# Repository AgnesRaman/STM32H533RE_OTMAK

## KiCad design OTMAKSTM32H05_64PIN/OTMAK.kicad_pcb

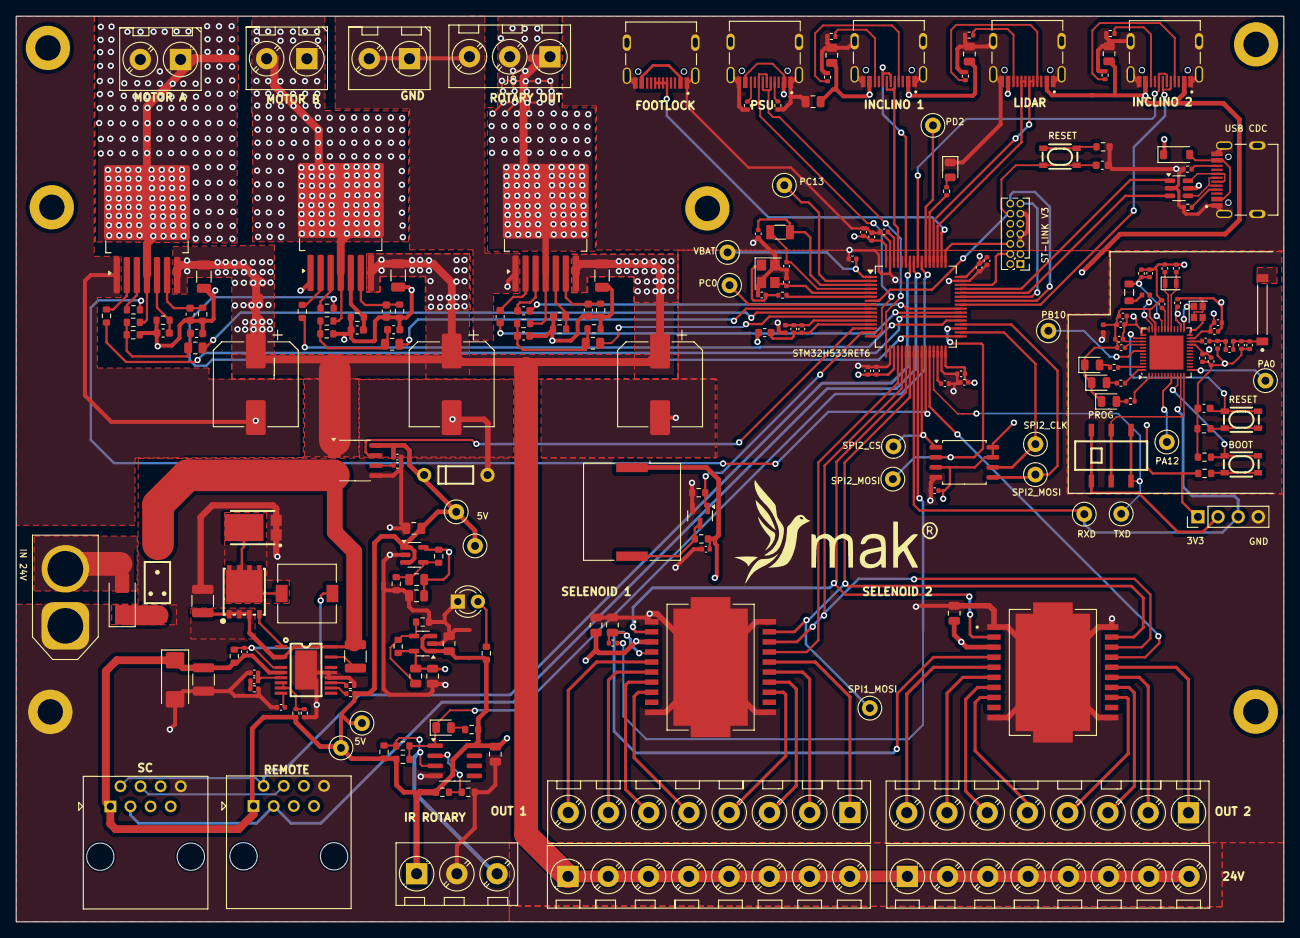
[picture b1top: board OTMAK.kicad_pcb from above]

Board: 4 copper layers, 160.0 x 114.3 mm, 227 parts (0 on the bottom side), 162 nets.

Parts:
ANT1: 2500AT44M0400E; 2500AT44M0400
BZ1: Buzzer; Buzzer_Murata_PKLCS1212E
C1, C33, C48, C53, C67: 100nF; C_0603_1608Metric
C2, C3: 24pF; C_0402_1005Metric
C4, C5: 5pF; C_0402_1005Metric
C6, C7: 2.2uF; C_0402_1005Metric
C8, C9, C10, C11, C16, C19, C29, C30, C31, C32, C34, C41, C45, C58: 100nF; C_0402_1005Metric
C12, C13, C14, C15, C69, C70: 1uF; C_0402_1005Metric
C17: 1UF; C_0402_1005Metric
C18: 10uF; C_0402_1005Metric
C20: 0.1uF; C_0805_2012Metric
C22, C23, C54, C75: 4.7uF; C_0805_2012Metric
C24, C25, C26, C60: 22uF; C_0805_2012Metric
C27, C50, C68: 1nF; C_0603_1608Metric
C28, C38: 4.7uF; C_0402_1005Metric
C35: 220nF; C_0402_1005Metric
C36, C37: 8pF; C_0402_1005Metric
C39: 3.4pF; C_0402_1005Metric
C40: 1.2pF; C_0402_1005Metric
C42, C44: 0.5pF; C_0402_1005Metric
C43, C46, C47: 3pF; C_0402_1005Metric
C49, C56, C65: 1uF; C_0603_1608Metric
C51, C59, C64: 100nF; C_1206_3216Metric
C52, C62, C63: 470uF/1000uF; CP_Elec_10x10.5
C55, C57, C76, C88: 4.7nF; C_0805_2012Metric
C66: 1uF; C_0805_2012Metric
C71: 3.3nF; C_0402_1005Metric
C72: 0.47uF; C_1210_3225Metric
C73: 47pF; C_0402_1005Metric
C74: 12uF; C_1210_3225Metric
C77: 0.1uF; C_0402_1005Metric
C78: 1nF; C_0402_1005Metric
C80: 330uF; CP_EIA-6032-15_Kemet-U
C83: 10uF; C_1210_3225Metric
COM-TO-STM1: SW-SMD_SS-3235S-L2
D1, D3, D4, D5: LED; LED_0805_2012Metric
D2: D; D_SOD-123
D6: D; LED_0805_2012Metric
D7: 1N5819; D_SMA
D8: S310; POWERDI-5_L5.4-W4.0-LS6.5-RD
D10: LED; LED_D3.0mm
F1: Fuse; RES-SMD_SA72SB0
FB1: 600 @ 100mhz; L_0603_1608Metric
H1, H3, H4, H5, H6, H7: MountingHole; MountingHole_3.2mm_M3_DIN965_Pad
J1, J2, J3, J4, J5, J14: TYPE-C-31-M-12; HRO_TYPE-C-31-M-12
J7: STLink; PinHeader_2x07_P1.27mm_Vertical
J8: ROTARY; TerminalBlock_3_Pin
J9: RX_DEBUG; TestPoint_Loop_D2.50mm_Drill1.0mm
J10: TX_DEBUG; TestPoint_Loop_D2.50mm_Drill1.0mm
J11: Conn_01x01; TestPoint_Loop_D2.50mm_Drill1.0mm
J12, J13, J15, J16: Conn_01x08; TerminalBlock_8_pin
J17: PROG; PinHeader_1x04_P2.54mm_Vertical
J18: IR Interrupt; TerminalBlock_3_Pin
J19, J20, J22: Conn_01x02; TerminalBlock_2_Pin
J21: 24V INPUT; AMASS_XT60-F_1x02_P7.20mm_Vertical
L1, L2: L; L_0402_1005Metric
L3: 10uH; L_0805_2012Metric
L4: 22nH; L_0402_1005Metric
L5: 3n; L_0402_1005Metric
L6: 22uH; L_7.3x7.3_H3.5
Q1: BSS138; SOT-23
R1, R2, R5, R7, R8, R9, R10, R12, R35, R38: 5k1; R_0402_1005Metric
R3, R18, R20: 100R; R_0603_1608Metric
R4: 47R; R_0402_1005Metric
R6, R33: 52.3K; R_0603_1608Metric
R11: 3M3; R_0603_1608Metric
R13, R17, R28, R58, R59, R63: 1K; R_0603_1608Metric
R14, R34: 30.1K; R_0603_1608Metric
R15: 100R; R_0402_1005Metric
R16, R23, R24, R25: 1K; R_0402_1005Metric
R19, R26: 10K; C_0603_1608Metric
R21: 100K; R_0603_1608Metric
R27, R37, R53: 0.51K; R_0603_1608Metric
R29, R40, R49: 3.9K; R_0603_1608Metric
R30, R45, R47: 33K; R_0603_1608Metric
R31, R36, R50, R51, R52, R54, R55, R56, R57: 10K; R_0603_1608Metric
R32, R46, R48: 0R; R_0805_2012Metric
R60: 5.76K; R_0402_1005Metric
R61: 36.5K; R_0402_1005Metric
R62: 20mR; R_0603_1608Metric
R64: 100K; R_0402_1005Metric
R65: 422K; R_0402_1005Metric
R66: 80.6K; R_0402_1005Metric
Remote1: RJ45; RJ45_OST_PJ012-8P8CX_Vertical
SC1: RJ45; RJ45_OST_PJ012-8P8CX_Vertical
SW1, SW3: EN; KEY-SMD_4P-L4.2-W3.2-P2.20-LS4.6
SW4: BOOT_; KEY-SMD_4P-L4.2-W3.2-P2.20-LS4.6
TP1, TP2, TP3, TP4, TP5, TP6, TP7, TP8, TP9, TP10, TP11, TP12, TP13, TP14, TP15: TestPoint_Loop_D2.50mm_Drill1.0mm
U1: LQFP-64_10x10mm_P0.5mm
U2: W25Q128JVSIQ; SOIC-8_5.275x5.275mm_P1.27mm
U3, U5: IC_L6201PS
U4, U8: TPS73601DBVR; TSOT-23-5
U6: QFN48; QFN-48-1EP_6x6mm_P0.4mm_EP4.3x4.3mm
U7, U9, U10: TO-263-7_TabPin8
U11: LM393; SOIC-8_3.9x4.9mm_P1.27mm
U12: CC6900SO-20A; SOP-8_3.9x4.9mm_P1.27mm
U13: TSSOP-20_L6.5-W4.4-P0.65-BL-EP
U14: AP3P3R0MT
U16: USBLC6-2SC6; SOT-23-6
Y1: 24MHz, 6pF; Crystal_SMD_3225-4Pin_3.2x2.5mm
Y2: 32.768 kHz; Crystal_SMD_3215-2Pin_3.2x1.5mm
Y3: 32.7680 KHz 12.5 pF; Crystal_SMD_2012-2Pin_2.0x1.2mm
Y4: 32.0000 MHz 8pF; Crystal_SMD_2016-4Pin_2.0x1.6mm
ZD1: BZX55C5V1; DO-35_BD2.0-L4.0-P8.00-D0.5-FD

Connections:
3.3VA: C55.1, C57.1, FB1.1, R33.1, U8.5 (OUT)
3V3: BZ1.1 (-), C8.2, C9.2, C10.2, C11.2, C12.2, C13.2, C14.2, C15.2, C18.2, C19.1, C30.1, C32.2, C34.2, C38.2, C41.2, C43.2, C45.1, C47.1, C76.1, C88.1, J7.3, J17.1, R6.1, R13.2, R18.1, U1.19 (VDD), U1.32 (VDD), U1.48 (VDD), U1.64 (VDD), U2.3 (~WP), U2.7 (~HOLD), U2.8 (VCC), U4.5 (OUT), U6.21 (VDD2), U6.23 (VDDRF), U6.26 (VDD4), U6.36 (VDDSD), U6.37 (VDD3), U6.39 (VDD1)
5V: C22.1, C23.1, C24.1, C25.1, C26.1, C54.1, C60.1, C66.1, C69.1, C75.1, C78.2, C80.1, C83.1, D2.1 (K), J1.A4B9 (VBUS), J1.B4A9 (VBUS), J2.A4B9 (VBUS), J2.B4A9 (VBUS), J3.A4B9 (VBUS), J3.B4A9 (VBUS), J14.A4B9 (VBUS), J14.B4A9 (VBUS), J18.1, R50.1, R51.1, R57.1, R59.1, R62.2, R63.1, R64.2, R65.2, Remote1.1, SC1.1, TP7.1, TP9.1, TP11.1, TP12.1, U3.3 (VDD), U4.1 (IN), U4.3 (EN), U5.3 (VDD), U8.1 (IN), U8.3 (EN), U11.8 (V+), U12.8 (VCC), U13.6 (SENSE-), U16.5 (VBUS), ZD1.2 (K)
/OSCIN: C2.2, U1.5 (PH0-OSC_IN), Y1.3
/OSCOUT: R4.2, U1.6 (PH1-OSC_OUT)
ADC1_INP0: U1.14 (PA0), U12.7 (VIOUT)
ADC1_INP12: R48.1, U1.10 (PC2)
ADC2_INP11: R46.1, U1.9 (PC1)
ADC2_INP13: R32.1, U1.11 (PC3)
BOOTA: R21.1, SW4.1, SW4.2, U6.10 (PA10)
C_D+: J5.A6 (DP1), J5.B6 (DP2), U16.6 (I/O1)
C_D-: J5.A7 (DN1), J5.B7 (DN2), U16.4 (I/O1)
GNDREF: C28.2, C29.2, C30.2, C31.2, C32.1, C33.2, C34.1, C35.1, C36.2, C37.2, C38.1, C40.1, C41.1, C43.1, C44.1, C45.2, C46.1, C47.2, D3.1 (K), D4.1 (K), D5.1 (K), L2.2, R20.2, R21.2, U6.34 (VSS), U6.49 (GND), Y4.2, Y4.4
I2C1_SCL: J1.A7 (DN1), J1.B7 (DN2), U1.61 (PB8)
I2C1_SDA: J1.A6 (DP1), J1.B6 (DP2), U1.59 (PB7)
I2C3_SCL: J3.A7 (DN1), J3.B7 (DN2), U1.41 (PA8)
I2C3_SDA: J3.A6 (DP1), J3.B6 (DP2), U1.56 (PB4)
IN-24V: C51.1, C52.1, C59.1, C62.1, C63.1, C64.1, J13.1, J13.2, J13.3, J13.4, J13.5, J13.6, J13.7, J13.8, J16.1, J16.2, J16.3, J16.4, J16.5, J16.6, J16.7, J16.8, U7.7 (VS), U9.7 (VS), U10.7 (VS), U12.1 (IP+), U12.2 (IP+)
INPUT_Foot_LOCK: J4.A6 (DP1), J4.A7 (DN1), J4.B6 (DP2), J4.B7 (DN2), U1.50 (PA15)
INT: Remote1.4, SC1.4
LD1: R16.1, U1.53 (PC12)
MOTOR_A: J19.1, J19.2, R45.1, U9.4 (OUT), U9.8 (OUT)
MOTOR_B: J20.1, J20.2, R47.1, U10.4 (OUT), U10.8 (OUT)
NRST: C1.2, J7.12, SW1.1, SW1.2, U1.7 (NRST)
unnamed: ANT1.1 (Feeding_Point), C42.2, C44.2, C46.2, L5.2
unnamed: BZ1.2 (+), Q1.3 (D), R13.1
unnamed: C3.2, R4.1, Y1.1
unnamed: C39.2, C40.2, C42.1, L5.1
unnamed: C49.1, R29.1, R30.2, R32.2
unnamed: C56.1, R40.1, R45.2, R46.2
unnamed: C65.1, R47.2, R48.2, R49.1
unnamed: C71.2, R60.2
unnamed: D1.2 (A), R16.2
unnamed: D2.2 (A), J5.A4B9 (VBUS), J5.B4A9 (VBUS)
unnamed: D3.2 (A), R23.2
unnamed: D4.2 (A), R24.2
unnamed: D5.2 (A), R25.2
unnamed: D6.2 (A), R59.2
unnamed: D7.2 (A), J21.2
unnamed: D7.1 (K), F1.1
unnamed: D8.3 (K), L6.1, U14.5 (D), U14.6 (D), U14.7 (D), U14.8 (D), U14.9 (D)
unnamed: D10.2 (A), R63.2
unnamed: J1.A5 (CC1), R1.2
unnamed: J1.B5 (CC2), R5.1
unnamed: J2.A5 (CC1), R2.2
unnamed: J2.B5 (CC2), R7.1
unnamed: J3.A5 (CC1), R9.2
unnamed: J3.B5 (CC2), R10.1
unnamed: J4.A4B9 (VBUS), J4.B4A9 (VBUS)
unnamed: J5.A5 (CC1), R8.2
unnamed: J5.B5 (CC2), R12.1
unnamed: J14.A5 (CC1), R35.2
unnamed: J14.B5 (CC2), R38.1
unnamed: COM-TO-STM1.1, COM-TO-STM1.4, J17.2
unnamed: J18.3, R50.2, R54.1, U11.3 (+)
unnamed: L3.2, L4.2
unnamed: R3.1, SW1.3, SW1.4
unnamed: R18.2, SW4.3, SW4.4
unnamed: R20.1, SW3.3, SW3.4
unnamed: C4.2, U1.3 (PC14-OSC32_IN), Y2.2
unnamed: C5.2, U1.4 (PC15-OSC32_OUT), Y2.1
unnamed: C58.1, TP1.1, U1.1 (VBAT)
unnamed: C76.2, R6.2, R14.1, U4.4 (NR/FB)
unnamed: U6.25 (OSCIN), Y4.1
unnamed: U6.24 (OSCOUT), Y4.3
unnamed: TP13.1, U6.13 (PA0)
unnamed: TP15.1, U6.8 (PA12)
unnamed: TP14.1, U6.42 (PB10)
unnamed: C39.1, U6.22 (RF1)
unnamed: C35.2, U6.31 (VCAP)
unnamed: C31.1, U6.40 (VDDA)
unnamed: C28.1, C29.1, L3.1, U6.32 (VFBSD)
unnamed: L4.1, U6.35 (VLXSD)
unnamed: C36.1, U6.30 (XTAL0), Y3.1
unnamed: C37.1, U6.29 (XTAL1), Y3.2
unnamed: R19.2, U7.2 (IN)
unnamed: R26.2, U7.3 (INH)
unnamed: C27.1, R17.2, U7.6 (IS)
unnamed: C48.1, R27.2, U7.5 (SR)
unnamed: C55.2, R33.2, R34.1, U8.4 (NR/FB)
unnamed: R31.2, U9.2 (IN)
unnamed: R36.2, U9.3 (INH)
unnamed: C50.1, R28.2, U9.6 (IS)
unnamed: C53.1, R37.2, U9.5 (SR)
unnamed: R56.1, U10.2 (IN)
unnamed: R55.1, U10.3 (INH)
unnamed: C68.1, R58.2, U10.6 (IS)
unnamed: C67.1, R53.2, U10.5 (SR)
unnamed: R51.2, R52.1, U11.2 (-)
unnamed: C70.1, U12.6 (FILTER)
unnamed: C72.2, U13.18 (CAP)
unnamed: R61.2, U13.13 (FREQ)
unnamed: U13.1 (GATE), U14.4 (G)
unnamed: C71.1, C73.1, U13.7 (ITH)
unnamed: R64.1, U13.12 (PGOOD)
unnamed: R65.1, R66.2, U13.8 (PGUV), U13.9 (VFB)
unnamed: C72.1, C74.1, F1.2, U12.3 (IP-), U12.4 (IP-), U13.3 (RUN), U13.20 (VIN), U14.1 (S), U14.2 (S), U14.3 (S)
unnamed: C78.1, L6.2, R62.1, U13.5 (SENS+)
unnamed: C77.1, U13.10 (TRACK/SS)
OUT0: J12.1, U3.16 (OUT0)
OUT0A: J15.1, U5.16 (OUT0)
OUT1: J12.2, U3.15 (OUT1)
OUT1A: J15.2, U5.15 (OUT1)
OUT2: J12.3, U3.14 (OUT2)
OUT2A: J15.3, U5.14 (OUT2)
OUT3: J12.4, U3.13 (OUT3)
OUT3A: J15.4, U5.13 (OUT3)
OUT4: J12.5, U3.8 (OUT4)
OUT4A: J15.5, U5.8 (OUT4)
OUT5: J12.6, U3.7 (OUT5)
OUT5A: J15.6, U5.7 (OUT5)
OUT6: J12.7, U3.6 (OUT6)
OUT6A: J15.7, U5.6 (OUT6)
OUT7: J12.8, U3.5 (OUT7)
OUT7A: J15.8, U5.5 (OUT7)
PB3_LED: R25.1, U6.1 (PB3)
PB4_LED: R24.1, U6.48 (PB4)
PB5_LED: R23.1, U6.47 (PB5)
PC0: TP8.1, U1.8 (PC0)
PC13: TP10.1, U1.2 (PC13)
PD2: TP2.1, U1.54 (PD2)
RESET: C20.1, R15.2, U3.4 (RESET), U5.4 (RESET)
ROTARY_DC_OUT: J8.1, J8.2, R30.1, U7.4 (OUT), U7.8 (OUT)
RSTN: C33.1, SW3.1, SW3.2, U6.38 (RSTN)
Rotary_GPIO_Read: D6.1 (K), R54.2, R57.2, U1.55 (PB3), U11.1
SPI1_CS1: U1.20 (PA4), U3.17 (CE)
SPI1_CS2: U1.28 (PB2), U5.17 (CE)
SPI1_MISO: U1.22 (PA6), U3.2 (SO), U5.2 (SO)
SPI1_MOSI: J11.1, U1.23 (PA7), U3.19 (SI), U5.19 (SI)
SPI1_RESET: R15.1, U1.25 (PC5)
SPI1_SCK: U1.21 (PA5), U3.18 (SCLK), U5.18 (SCLK)
SPI2_CLK: TP4.1, U1.34 (PB13), U2.6 (SCK)
SPI2_CS: TP3.1, U1.26 (PB0), U2.1 (~CS)
SPI2_MISO: TP6.1, U1.35 (PB14), U2.2 (DO(IO1))
SPI2_MOSI: TP5.1, U1.36 (PB15), U2.5 (DI(IO0))
SWCLK: J7.6, U1.49 (PA14)
SWDIO: J7.4, U1.46 (PA13)
TIM2_CH2_BUZZER: Q1.1 (G), R11.2, U1.15 (PA1)
TIM3_CH1: R31.1, U1.37 (PC6)
TIM3_CH2: R56.2, U1.38 (PC7)
TIM3_CH3: R19.1, U1.39 (PC8)
TIM3_CH4: R55.2, U1.27 (PB1)
TIM8_CH3: R36.1, U1.33 (PB12)
TIM8_CH4: R26.1, U1.40 (PC9)
UART4_RX_LIDAR: J2.A6 (DP1), J2.B7 (DN2), U1.52 (PC11)
UART4_TX_LIDAR: J2.A7 (DN1), J2.B6 (DP2), U1.51 (PC10)
UART5_RX_SC: Remote1.3, SC1.3, U1.57 (PB5)
UART5_TX_SC: Remote1.2, SC1.2, U1.58 (PB6)
UART_RX: COM-TO-STM1.2, COM-TO-STM1.5, U6.12 (PA8)
USART1_RX_ST-LINK: J7.13, U1.43 (PA10)
USART1_TX_ST-LINK: J7.14, U1.42 (PA9)
USART2_RX_PSU: J14.A7 (DN1), J14.B7 (DN2), U1.17 (PA3)
USART2_TX_PSU: J14.A6 (DP1), J14.B6 (DP2), U1.16 (PA2)
USART3_RX_STM: J9.1, J17.3, U1.24 (PC4), U6.11 (PA9)
USART3_TX_STM: COM-TO-STM1.3, COM-TO-STM1.6, J10.1, U1.29 (PB10)
USB-DM: U1.44 (PA11), U16.3 (I/O2)
USB-DP: U1.45 (PA12), U16.1 (I/O2)
VCAP1: C6.2, U1.30 (VCAP1)
VCAP2: C7.2, U1.62 (VCAP2)
VDDA: C16.2, C17.2, FB1.2, U1.13 (VDDA/VREF+)
VSS: C1.1, C2.1, C3.1, C4.1, C5.1, C6.1, C7.1, C8.1, C9.1, C10.1, C11.1, C12.1, C13.1, C14.1, C15.1, C18.1, C19.2, C20.2, C22.2, C23.2, C24.2, C25.2, C26.2, C27.2, C48.2, C49.2, C50.2, C51.2, C52.2, C53.2, C54.2, C56.2, C57.2, C58.2, C59.2, C60.2, C62.2, C63.2, C64.2, C65.2, C66.2, C67.2, C68.2, C69.2, C70.2, C73.2, C74.2, C75.2, C77.2, C80.2, C83.2, C88.2, D1.1 (K), D8.1 (A), D8.2 (A), D10.1 (K), H3.1, J1.A1B12 (GND), J1.B1A12 (GND), J1.S1 (SHIELD), J1.S2 (SHIELD), J1.S3 (SHIELD), J1.S4 (SHIELD), J2.A1B12 (GND), J2.B1A12 (GND), J2.S1 (SHIELD), J2.S2 (SHIELD), J2.S3 (SHIELD), J2.S4 (SHIELD), J3.A1B12 (GND), J3.B1A12 (GND), J3.S1 (SHIELD), J3.S2 (SHIELD), J3.S3 (SHIELD), J3.S4 (SHIELD), J4.A1B12 (GND), J4.B1A12 (GND), J4.S1 (SHIELD), J4.S2 (SHIELD), J4.S3 (SHIELD), J4.S4 (SHIELD), J5.A1B12 (GND), J5.B1A12 (GND), J5.S1 (SHIELD), J5.S2 (SHIELD), J5.S3 (SHIELD), J5.S4 (SHIELD), J7.5, J7.7, J7.11, J8.3, J14.A1B12 (GND), J14.B1A12 (GND), J14.S1 (SHIELD), J14.S2 (SHIELD), J14.S3 (SHIELD), J14.S4 (SHIELD), J17.4, J18.2, J21.1, J22.1, J22.2, L1.2, L2.1, Q1.2 (S), R1.1, R2.1, R3.2, R5.2, R7.2, R8.1, R9.1, R10.2, R11.1, R12.2, R14.2, R17.1, R27.1, R28.1, R29.2, R34.2, R35.1, R37.1, R38.2, R40.2, R49.2, R52.2, R53.1, R58.1, R60.1, R61.1, R66.1, Remote1.8, SC1.8, U1.18 (VSS), U1.31 (VSS), U1.47 (VSS), U1.63 (VSS), U2.4 (GND), U3.1 (GND), U3.10 (GND), U3.11 (GND), U3.20 (GND), U3.21 (EP), U4.2 (GND), U5.1 (GND), U5.10 (GND), U5.11 (GND), U5.20 (GND), U5.21 (EP), U7.1 (GND), U8.2 (GND), U9.1 (GND), U10.1 (GND), U11.4 (V-), U12.5 (GND), U13.14 (OVLO), U13.15 (EXTS), U13.21 (GND), U16.2 (GND), Y1.2, Y1.4, ZD1.1 (A)
VSSA: C16.1, C17.1, L1.1, U1.12 (VSSA/VREF-)

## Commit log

2024-12-05 "first commit"
2024-12-05 update skematik 241205_451
2024-12-06 revision skematik
2024-12-06 next revisi 241206 1656
2025-01-03 full version
